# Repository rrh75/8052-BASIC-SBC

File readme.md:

# MSC-51 mini 8052 BASIC single board computer 
This is a single board computer with Intel 8052 microcontioller, which runs special version of Microsoft BASIC.

This board actually work with Atmel AT8952 chip, has a 32KB of RAM and 8KB of flash memory for permanent program storage.

In the documentation folder there is a schematic in pdf and also the original Intel datasheet for specialized chip 8052AH-BASIC, which has a prewritten code to run BASIC.

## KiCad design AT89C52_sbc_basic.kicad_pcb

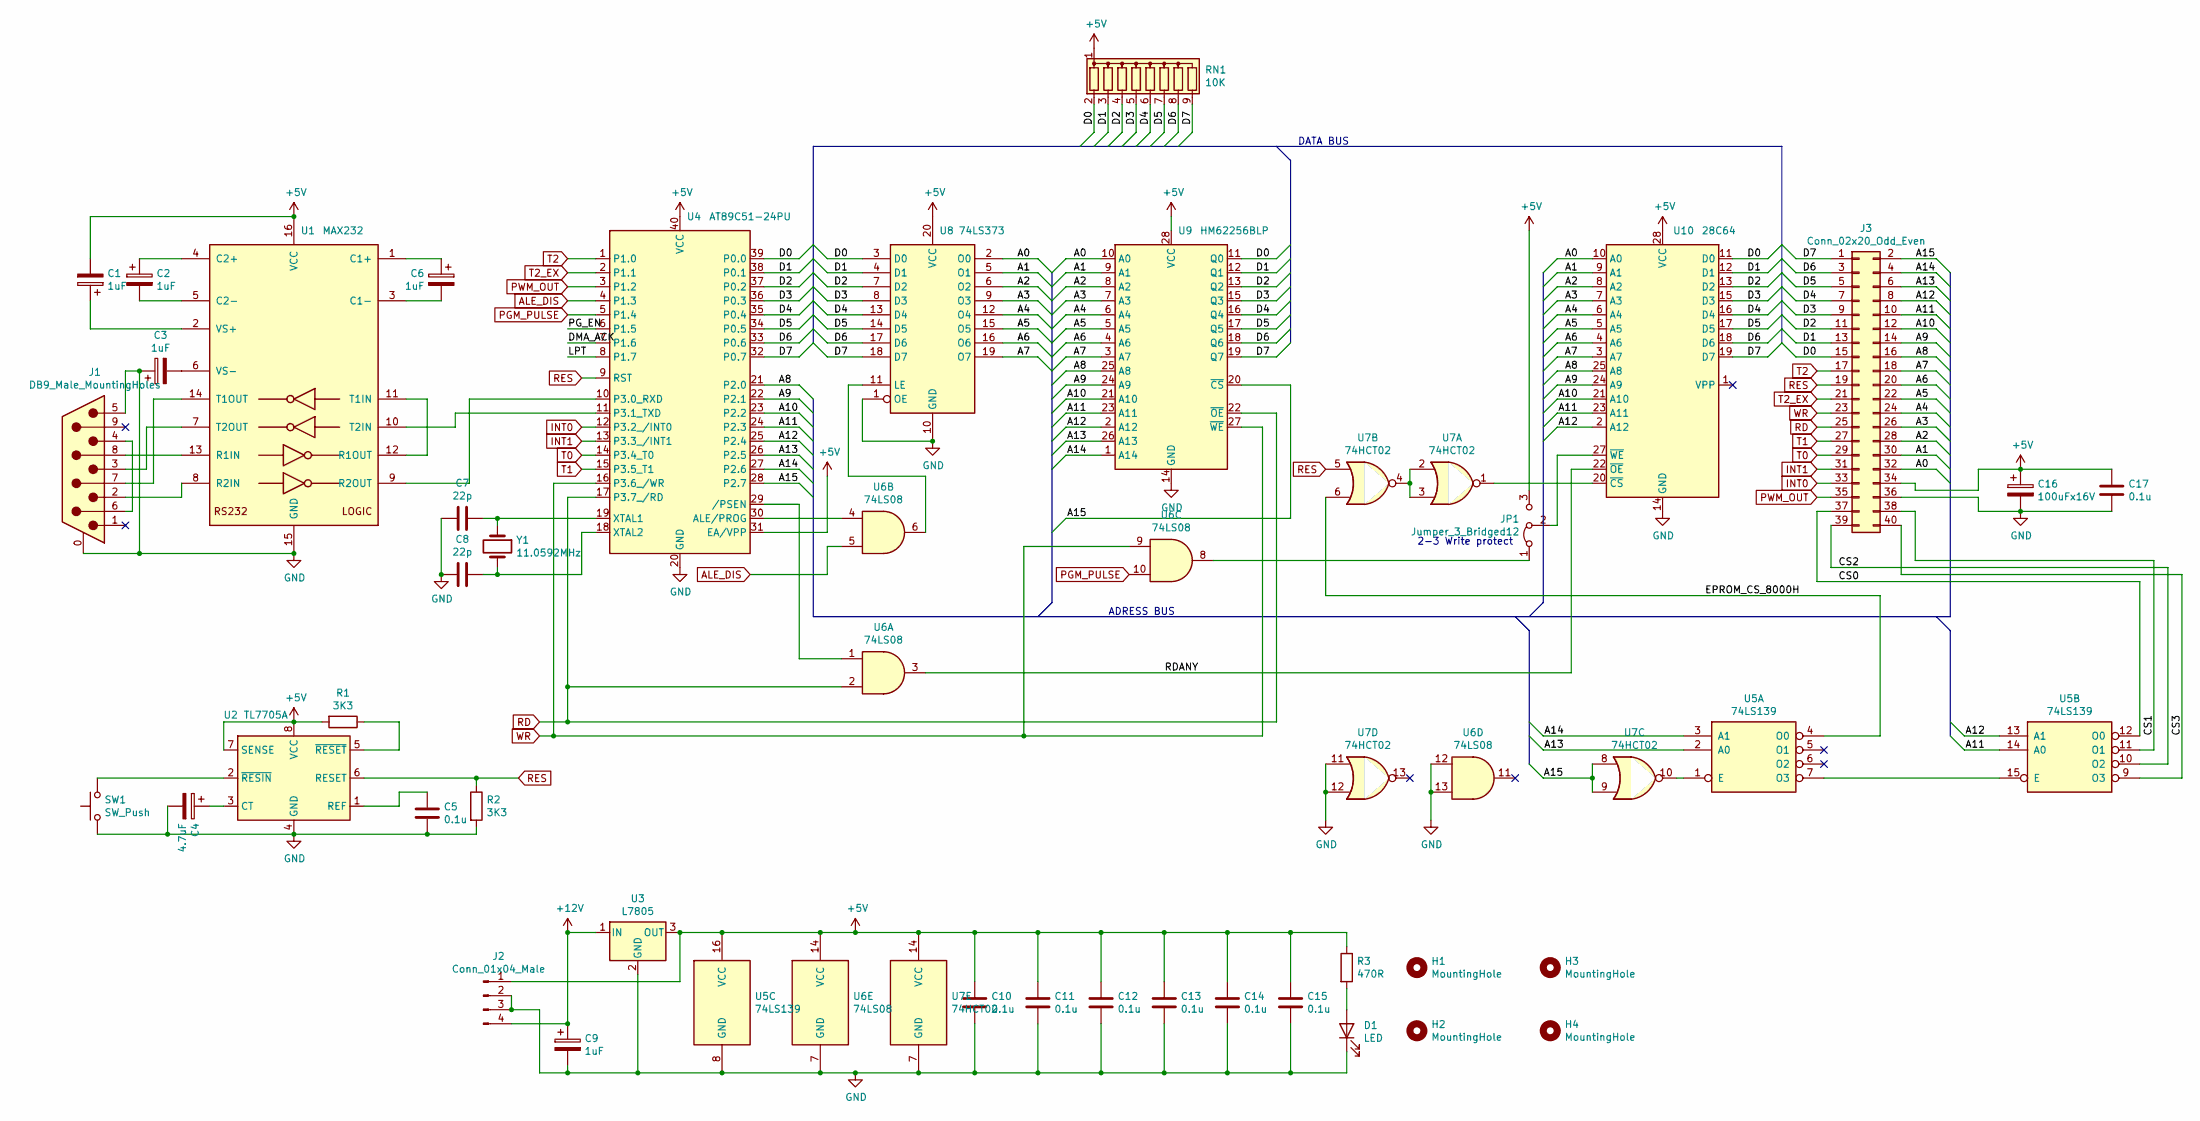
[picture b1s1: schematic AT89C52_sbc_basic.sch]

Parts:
C1, C2, C3, C6, C9: 1uF; CP_Radial_D5.0mm_P2.00mm
C4: 4.7uF; CP_Radial_D5.0mm_P2.00mm
C5, C10, C11, C12, C13, C14, C15, C17: 0.1u; C_Disc_D4.3mm_W1.9mm_P5.00mm
C7, C8: 22p; C_Disc_D4.3mm_W1.9mm_P5.00mm
C16: 100uFx16V; CP_Radial_D6.3mm_P2.50mm
D1: LED; LED_D3.0mm
H1, H2, H3, H4: MountingHole; MountingHole_2.7mm_M2.5
J1: DB9_Male_MountingHoles; DSUB-9_Male_Horizontal_P2.77x2.84mm_EdgePinOffset7.70mm_Hou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
J2: Conn_01x04_Male; Pin_Header_Angled_1x04_Pitch2.54mm
J3: Conn_02x20_Odd_Even; Pin_Header_Straight_2x20_Pitch2.54mm
JP1: Jumper_3_Bridged12; Pin_Header_Straight_1x03_Pitch2.54mm
R1, R2: 3K3; R_Axial_DIN0207_L6.3mm_D2.5mm_P7.62mm_Horizontal
R3: 470R; R_Axial_DIN0207_L6.3mm_D2.5mm_P7.62mm_Horizontal
RN1: 10K; R_Array_SIP9
SW1: SW_Push; SW_Tactile_SKHH_Angled
U1: MAX232; DIP-16_W7.62mm
U2: TL7705A; DIP-8_W7.62mm
U3: L7805; TO-220-3_Horizontal
U4: AT89C51-24PU; DIP-40_W15.24mm
U5: 74LS139; DIP-16_W7.62mm
U6: 74LS08; DIP-14_W7.62mm
U7: 74HCT02; DIP-14_W7.62mm
U8: 74LS373; DIP-20_W7.62mm
U9: HM62256BLP; DIP-28_W15.24mm
U10: 28C64; DIP-28_W15.24mm
Y1: 11.0592MHz; Crystal_HC49-U_Vertical

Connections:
+5V: C1.2, C10.1, C11.1, C12.1, C13.1, C14.1, C15.1, C16.1, C17.1, J2.1, J3.34, JP1.3 (B), R1.2, R3.1, RN1.1 (common), U1.16 (VCC), U2.7 (SENSE), U2.8 (VCC), U3.3 (OUT), U4.31 (EA/VPP), U4.40 (VCC), U5.16 (VCC), U6.14 (VCC), U7.14 (VCC), U8.20 (VCC), U9.28 (VCC), U10.28 (VCC)
+12V: C9.1, J2.4, U3.1 (IN)
/A0: J3.32, U8.2 (O0), U9.10 (A0), U10.10 (A0)
/A1: J3.30, U8.5 (O1), U9.9 (A1), U10.9 (A1)
/A2: J3.28, U8.6 (O2), U9.8 (A2), U10.8 (A2)
/A3: J3.26, U8.9 (O3), U9.7 (A3), U10.7 (A3)
/A4: J3.24, U8.12 (O4), U9.6 (A4), U10.6 (A4)
/A5: J3.22, U8.15 (O5), U9.5 (A5), U10.5 (A5)
/A6: J3.20, U8.16 (O6), U9.4 (A6), U10.4 (A6)
/A7: J3.18, U8.19 (O7), U9.3 (A7), U10.3 (A7)
/A8: J3.16, U4.21 (P2.0), U9.25 (A8), U10.25 (A8)
/A9: J3.14, U4.22 (P2.1), U9.24 (A9), U10.24 (A9)
/A10: J3.12, U4.23 (P2.2), U9.21 (A10), U10.21 (A10)
/A11: J3.10, U4.24 (P2.3), U5.14 (A0), U9.23 (A11), U10.23 (A11)
/A12: J3.8, U4.25 (P2.4), U5.13 (A1), U9.2 (A12), U10.2 (A12)
/A13: J3.6, U4.26 (P2.5), U5.2 (A0), U9.26 (A13)
/A14: J3.4, U4.27 (P2.6), U5.3 (A1), U9.1 (A14)
/A15: J3.2, U4.28 (P2.7), U7.8, U7.9, U9.20 (~CS)
/CS0: J3.37, U5.12 (O0)
/CS1: J3.38, U5.11 (O1)
/CS2: J3.39, U5.10 (O2)
/CS3: J3.40, U5.9 (O3)
/D0: J3.15, RN1.2 (R1), U4.39 (P0.0), U8.3 (D0), U9.11 (Q0), U10.11 (D0)
/D1: J3.13, RN1.3 (R2), U4.38 (P0.1), U8.4 (D1), U9.12 (Q1), U10.12 (D1)
/D2: J3.11, RN1.4 (R3), U4.37 (P0.2), U8.7 (D2), U9.13 (Q2), U10.13 (D2)
/D3: J3.9, RN1.5 (R4), U4.36 (P0.3), U8.8 (D3), U9.15 (Q3), U10.15 (D3)
/D4: J3.7, RN1.6 (R5), U4.35 (P0.4), U8.13 (D4), U9.16 (Q4), U10.16 (D4)
/D5: J3.5, RN1.7 (R6), U4.34 (P0.5), U8.14 (D5), U9.17 (Q5), U10.17 (D5)
/D6: J3.3, RN1.8 (R7), U4.33 (P0.6), U8.17 (D6), U9.18 (Q6), U10.18 (D6)
/D7: J3.1, RN1.9 (R8), U4.32 (P0.7), U8.18 (D7), U9.19 (Q7), U10.19 (D7)
/EPROM_CS_8000H: U5.4 (O0), U7.6
/RDANY: U6.3, U10.22 (~OE)
ALE_DIS: U4.4 (P1.3), U6.5
GND: C3.1, C4.2, C5.2, C7.2, C8.2, C9.2, C10.2, C11.2, C12.2, C13.2, C14.2, C15.2, C16.2, C17.2, D1.1 (K), J1.0 (PAD), J1.5, J2.2, J2.3, J3.36, R2.2, SW1.1, U1.15 (GND), U2.4 (GND), U3.2 (GND), U4.20 (GND), U5.8 (GND), U6.7 (GND), U6.12, U6.13, U7.7 (GND), U7.11, U7.12, U8.1 (OE), U8.10 (GND), U9.14 (GND), U10.14 (GND)
INT0: J3.33, U4.12 (P3.2_/INT0)
INT1: J3.31, U4.13 (P3.3_/INT1)
unnamed: C1.1, U1.2 (VS+)
unnamed: C2.1, U1.4 (C2+)
unnamed: C2.2, U1.5 (C2-)
unnamed: C3.2, U1.6 (VS-)
unnamed: C4.1, U2.3 (CT)
unnamed: C5.1, U2.1 (REF)
unnamed: C6.1, U1.1 (C1+)
unnamed: C6.2, U1.3 (C1-)
unnamed: C7.1, U4.19 (XTAL1), Y1.1
unnamed: C8.1, U4.18 (XTAL2), Y1.2
unnamed: D1.2 (A), R3.2
unnamed: J1.2, U1.8 (R2IN)
unnamed: J1.3, U1.7 (T2OUT)
unnamed: J1.4, J1.6
unnamed: J1.7, U1.14 (T1OUT)
unnamed: J1.8, U1.13 (R1IN)
unnamed: JP1.1 (A), U6.8
unnamed: JP1.2 (C), U10.27 (~WE)
unnamed: R1.1, U2.5 (~RESET)
unnamed: SW1.2, U2.2 (~RESIN)
unnamed: U1.9 (R2OUT), U4.10 (P3.0_RXD)
unnamed: U1.10 (T2IN), U4.11 (P3.1_TXD)
unnamed: U1.11 (T1IN), U1.12 (R1OUT)
unnamed: U4.29 (/PSEN), U6.1
unnamed: U4.30 (ALE/PROG), U6.4
unnamed: U5.1 (E), U7.10
unnamed: U5.7 (O3), U5.15 (E)
unnamed: U6.6, U8.11 (LE)
unnamed: U7.2, U7.3, U7.4
unnamed: U7.1, U10.20 (~CS)
PGM_PULSE: U4.5 (P1.4), U6.10
PWM_OUT: J3.35, U4.3 (P1.2)
RD: J3.25, U4.17 (P3.7_/RD), U6.2, U9.22 (~OE)
RES: J3.19, R2.1, U2.6 (RESET), U4.9 (RST), U7.5
T0: J3.29, U4.14 (P3.4_T0)
T1: J3.27, U4.15 (P3.5_T1)
T2: J3.17, U4.1 (P1.0)
T2_EX: J3.21, U4.2 (P1.1)
WR: J3.23, U4.16 (P3.6_/WR), U6.9, U9.27 (~WE)

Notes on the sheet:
DATA BUS
ADRESS BUS
2-3 Write protect

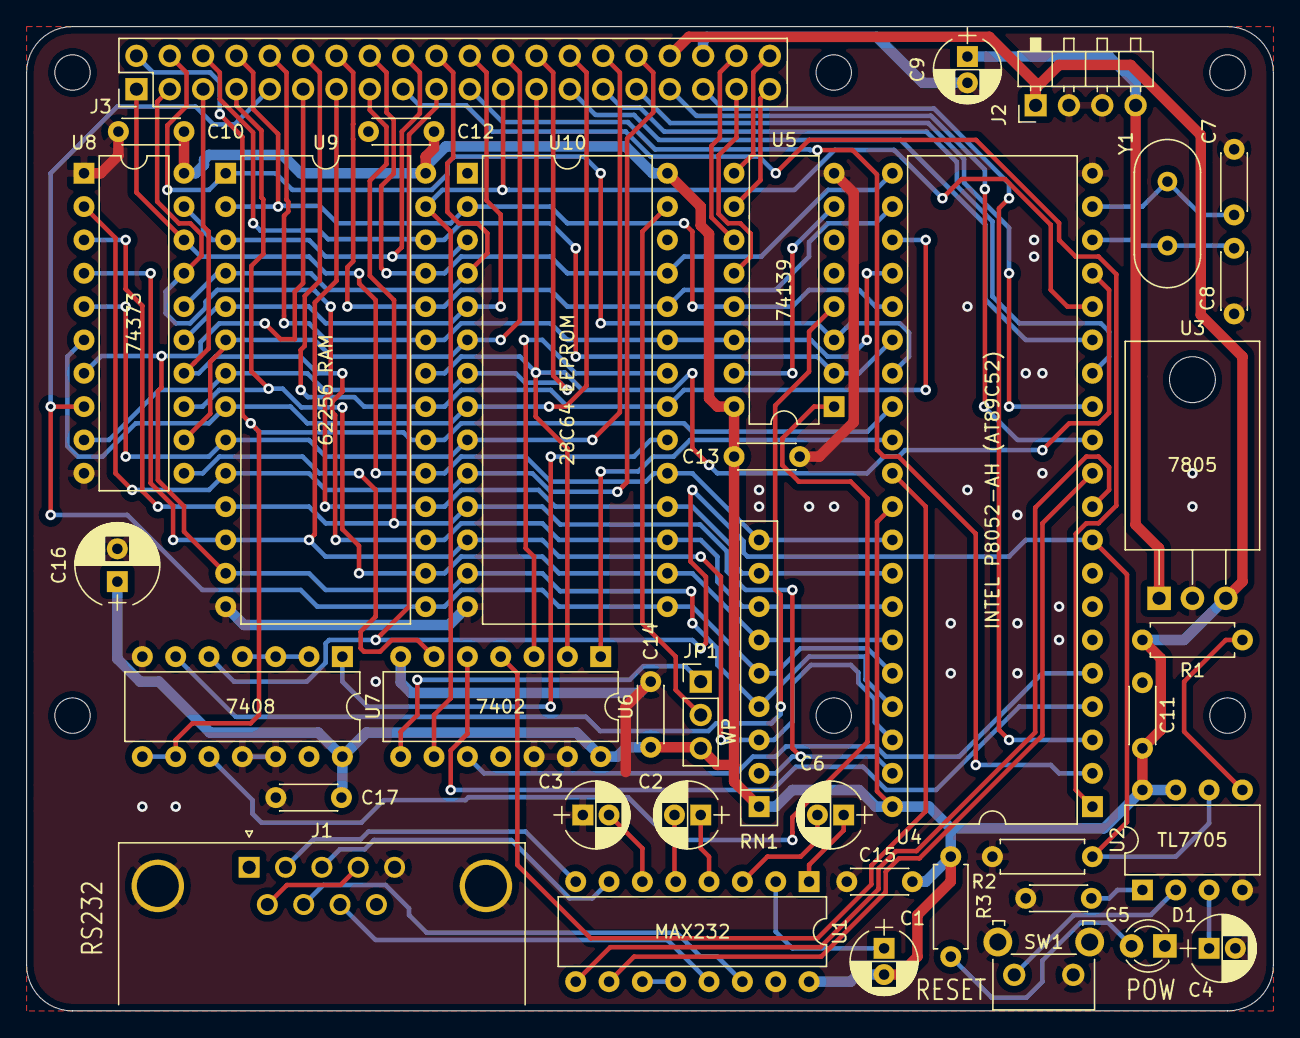
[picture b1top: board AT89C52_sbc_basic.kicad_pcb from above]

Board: 2 copper layers, 95.0 x 75.0 mm, 44 parts (0 on the bottom side), 75 nets.

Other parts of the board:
H1#2, H2#2: MountingHole; MountingHole_2.7mm_M2.5
